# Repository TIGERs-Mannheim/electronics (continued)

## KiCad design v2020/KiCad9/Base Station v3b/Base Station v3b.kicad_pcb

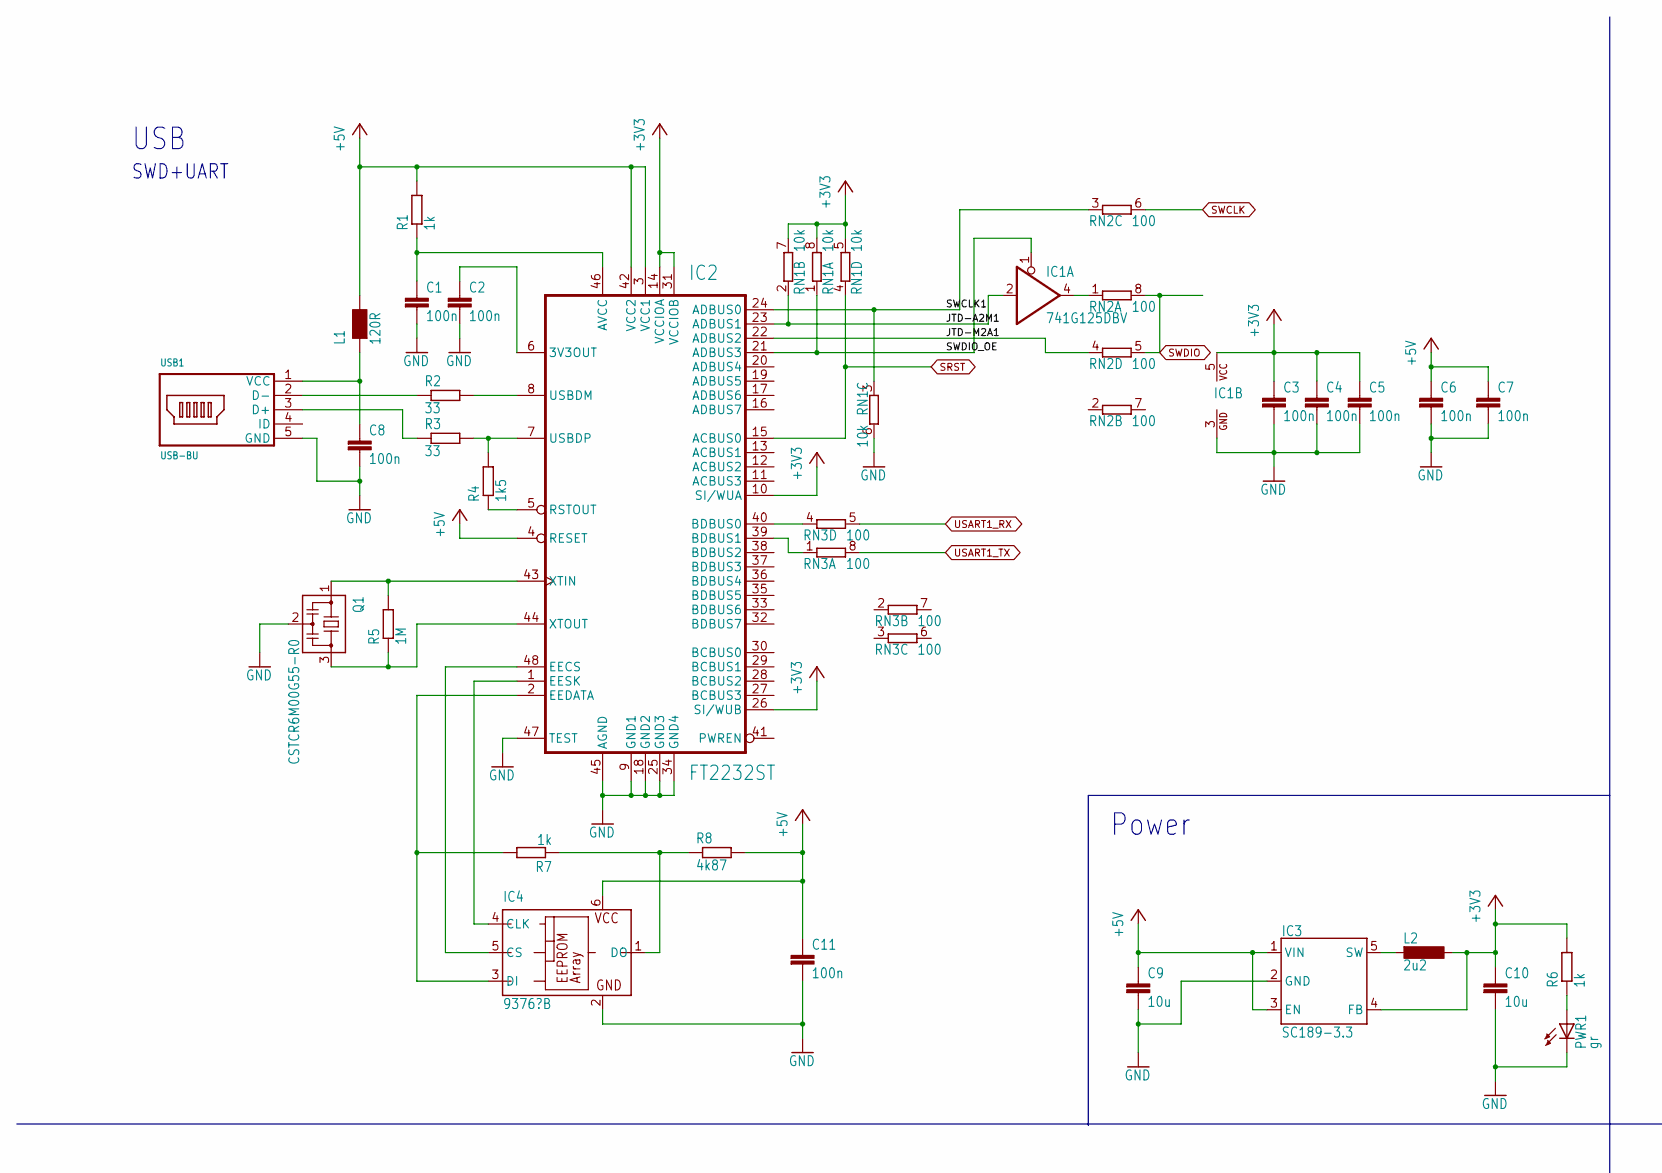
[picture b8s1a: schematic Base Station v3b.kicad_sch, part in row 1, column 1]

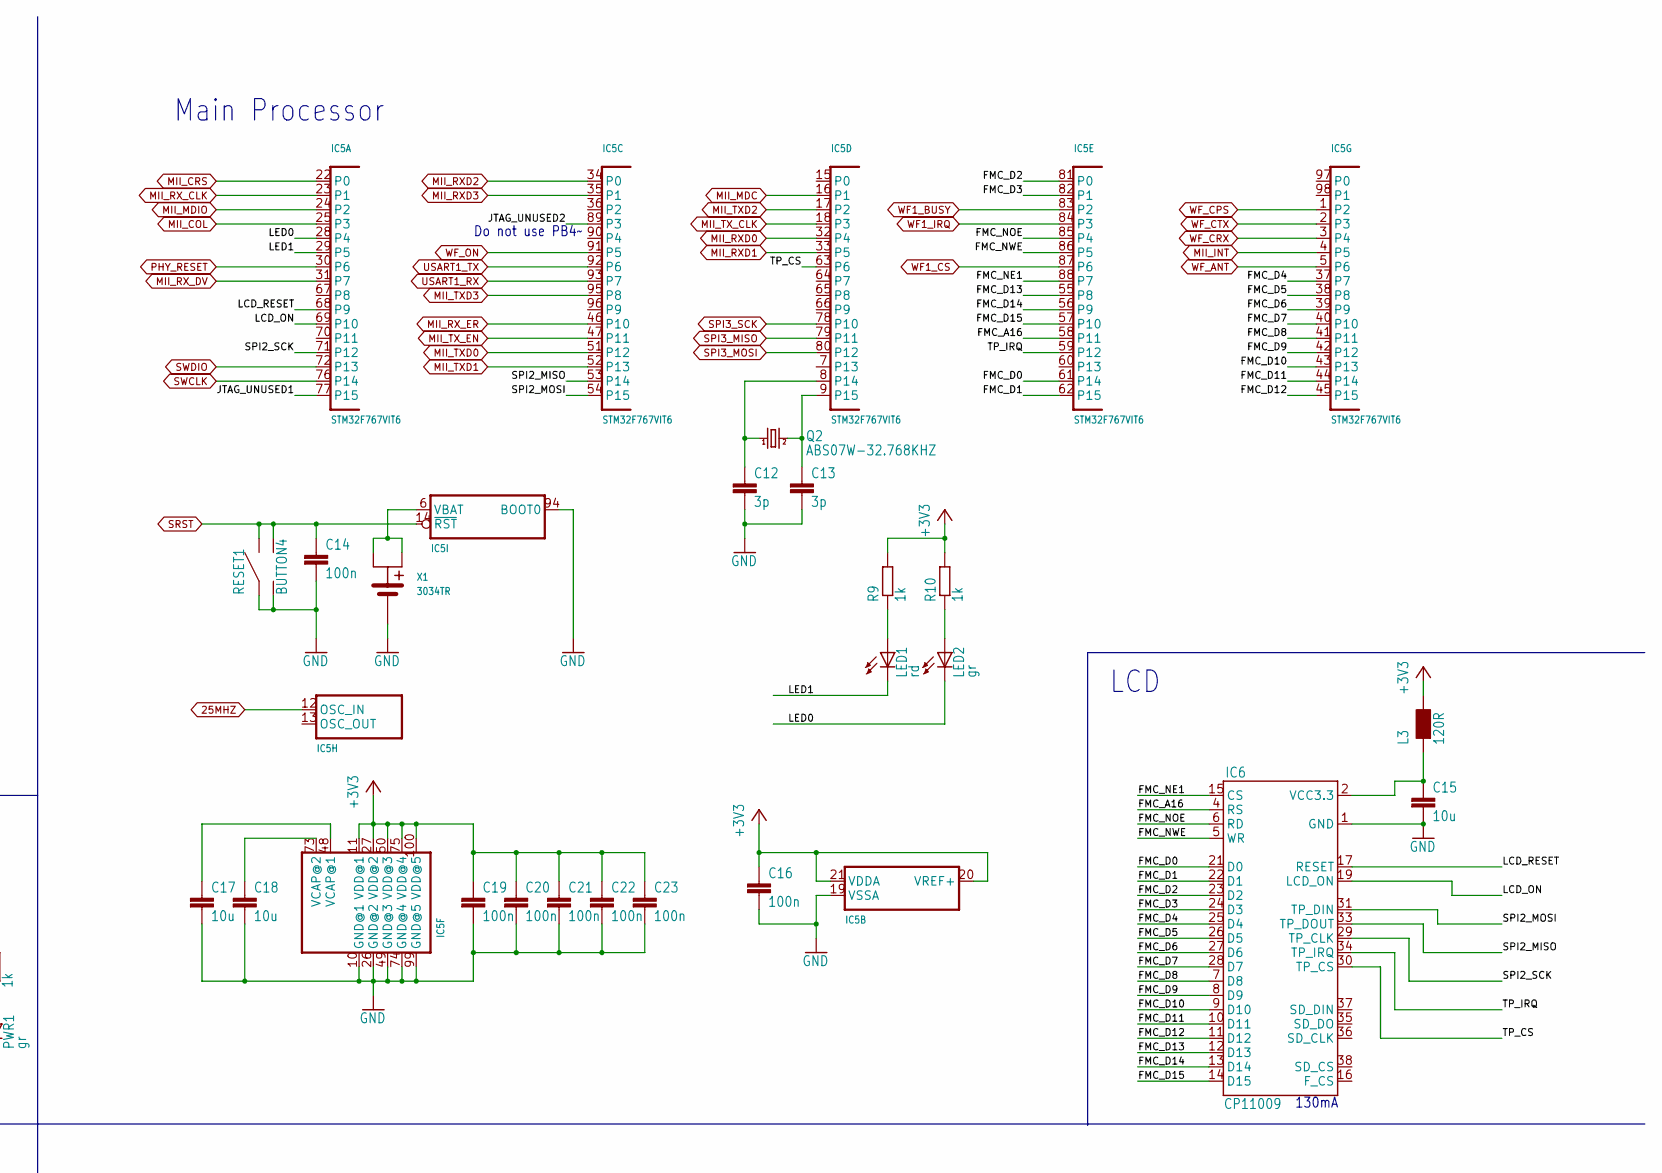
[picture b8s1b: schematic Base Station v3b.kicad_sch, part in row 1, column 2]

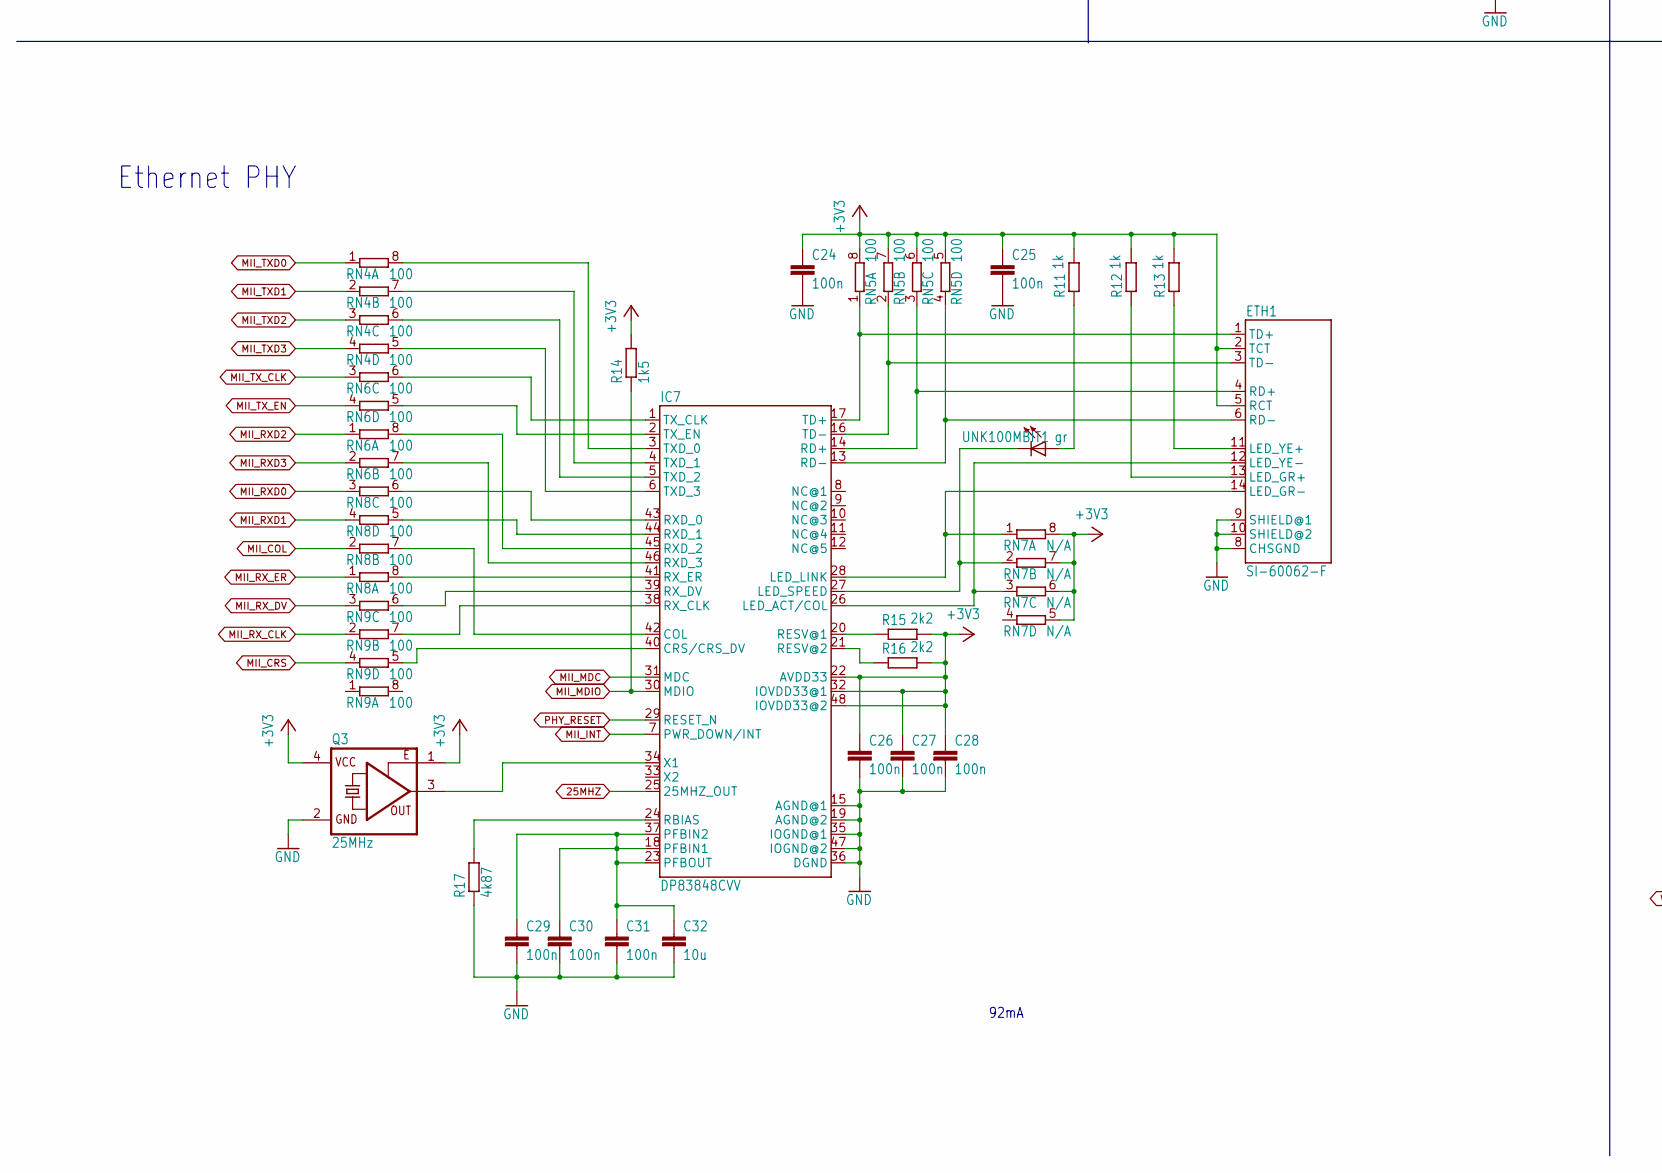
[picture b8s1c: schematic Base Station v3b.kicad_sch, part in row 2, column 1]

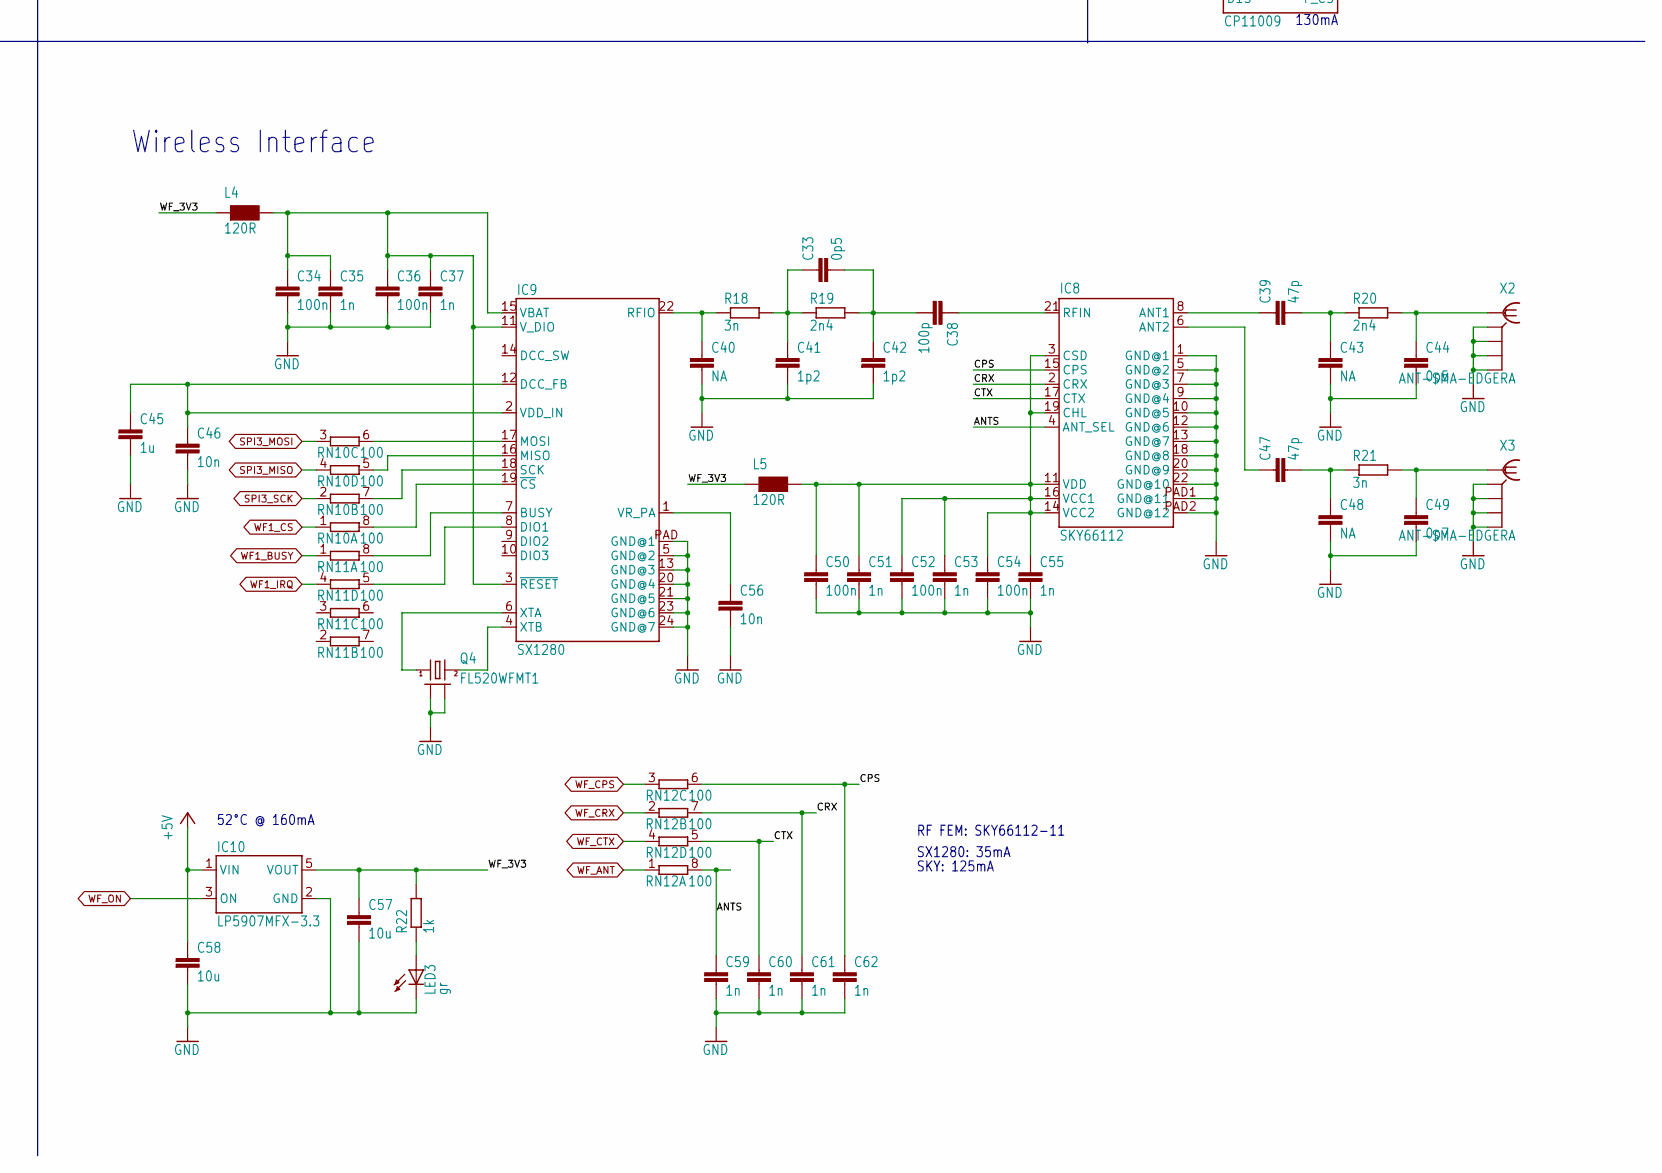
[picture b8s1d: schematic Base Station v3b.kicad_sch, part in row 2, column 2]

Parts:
C1, C2, C3, C4, C5, C6, C7, C8, C11, C14, C16, C19, C20, C21, C22, C23, C24, C25, C26, C27, C28, C29, C30, C31, C34, C36, C50, C52, C54: 100n; C0603
C9, C10, C15, C17, C18, C32, C57, C58: 10u; C0603
C12, C13: 3p; C0603
C33, C44: 0p5; C0402
C35, C37, C51, C53, C55, C59, C60, C61, C62: 1n; C0603
C38: 100p; C0402
C39, C47: 47p; C0402
C40, C43, C48: NA; C0402
C41, C42: 1p2; C0402
C45: 1u; C0603
C46, C56: 10n; C0603
C49: 0p7; C0402
ETH1: SI-60062-F; RJ45-LED
IC1: 741G125DBV; SOT23-5
IC2: FT2232ST; LQFP48-ST
IC3: SC189-3.3; SOT23-5
IC4: 9376?B; SOT23-6
IC5: STM32F767VIT6; LQFP100-ST
IC6: CP11009; CP11009-THX
IC7: DP83848CVV; LQFP48
IC8: SKY66112; SMCM-22
IC9: SX1280; QFN24L
IC10: LP5907MFX-3.3; SOT23-5L
L1, L3, L4, L5: 120R; 0603
L2: 2u2; IHLP1616
LED1: rd; CHIP-LED0603
LED2, LED3: gr; CHIP-LED0603
PWR1: gr; CHIP-LED0603
Q1: CSTCR6M00G55-R0; CSTCR6M
Q2: ABS07W-32.768KHZ; CRYSTAL-07W
Q3: 25MHz; 7X
Q4: FL520WFMT1; CRYSTAL-7M
R1, R6, R7, R9, R10, R11, R12, R13, R22: 1k; R0603
R2, R3: 33; R0603
R4, R14: 1k5; R0603
R5: 1M; R0603
R8, R17: 4k87; R0603
R15, R16: 2k2; R0603
R18, R21: 3n; R0402
R19, R20: 2n4; R0402
RESET1: BUTTON4
RN1: 10k; EXB28V
RN2, RN3, RN4, RN5, RN6, RN8, RN9, RN10, RN11, RN12: 100; EXB28V
RN7: N/A; EXB28V
UNK100MBIT1: gr; CHIP-LED0603
USB1: USB-BU; USB-BMICRO
X1: 3034TR; CR2025
X2, X3: ANT-SMA-EDGERA; ANT-SMA-RA

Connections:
25MHZ: IC5.12 (OSC_IN), IC7.25 (25MHZ_OUT)
+3V3: C3.1, C4.1, C5.1, C10.1, C16.1, C19.1, C20.1, C21.1, C22.1, C23.1, C24.1, C25.1, C26.1, C27.1, C28.1, ETH1.2 (TCT), ETH1.5 (RCT), IC1.5 (VCC), IC2.10 (SI/WUA), IC2.14 (VCCIOA), IC2.26 (SI/WUB), IC2.31 (VCCIOB), IC3.4 (FB), IC5.11 (VDD@1), IC5.20 (VREF+), IC5.21 (VDDA), IC5.27 (VDD@2), IC5.50 (VDD@3), IC5.75 (VDD@4), IC5.100 (VDD@5), IC7.22 (AVDD33), IC7.32 (IOVDD33@1), IC7.48 (IOVDD33@2), L2.P$1 (1), L3.2, Q3.1 (OE), Q3.4 (VCC), R6.2, R9.2, R10.2, R11.2, R12.2, R13.2, R14.2, R15.2, R16.2, RN1.5 (2), RN1.7 (2), RN1.8 (2), RN5.5 (2), RN5.6 (2), RN5.7 (2), RN5.8 (2), RN7.5 (2), RN7.6 (2), RN7.7 (2), RN7.8 (2); also elsewhere on the board
+5V: C6.1, C7.1, C9.1, C11.1, C58.1, IC2.3 (VCC1), IC2.4 (RESET), IC2.42 (VCC2), IC3.1 (VIN), IC3.3 (EN), IC4.6 (VCC), IC10.1 (VIN), L1.2, R1.2, R8.2
ANTS: C59.1, IC8.4 (ANT_SEL), RN12.8 (2)
CPS: C62.1, IC8.15 (CPS), RN12.6 (2)
CRX: C61.1, IC8.2 (CRX), RN12.7 (2)
CTX: C60.1, IC8.17 (CTX), RN12.5 (2)
FMC_A16: IC5.58 (P11), IC6.4 (RS)
FMC_D0: IC5.61 (P14), IC6.21 (D0)
FMC_D1: IC5.62 (P15), IC6.22 (D1)
FMC_D2: IC5.81 (P0), IC6.23 (D2)
FMC_D3: IC5.82 (P1), IC6.24 (D3)
FMC_D4: IC5.37 (P7), IC6.25 (D4)
FMC_D5: IC5.38 (P8), IC6.26 (D5)
FMC_D6: IC5.39 (P9), IC6.27 (D6)
FMC_D7: IC5.40 (P10), IC6.28 (D7)
FMC_D8: IC5.41 (P11), IC6.7 (D8)
FMC_D9: IC5.42 (P12), IC6.8 (D9)
FMC_D10: IC5.43 (P13), IC6.9 (D10)
FMC_D11: IC5.44 (P14), IC6.10 (D11)
FMC_D12: IC5.45 (P15), IC6.11 (D12)
FMC_D13: IC5.55 (P8), IC6.12 (D13)
FMC_D14: IC5.56 (P9), IC6.13 (D14)
FMC_D15: IC5.57 (P10), IC6.14 (D15)
FMC_NE1: IC5.88 (P7), IC6.15 (CS)
FMC_NOE: IC5.85 (P4), IC6.6 (RD)
FMC_NWE: IC5.86 (P5), IC6.5 (WR)
GND: C1.2, C2.2, C3.2, C4.2, C5.2, C6.2, C7.2, C8.2, C9.2, C10.2, C11.2, C12.2, C13.2, C14.2, C15.2, C16.2, C17.2, C18.2, C19.2, C20.2, C21.2, C22.2, C23.2, C24.2, C25.2, C26.2, C27.2, C28.2, C29.2, C30.2, C31.2, C32.2, C34.2, C35.2, C36.2, C37.2, C40.2, C41.2, C42.2, C43.2, C44.2, C45.2, C46.2, C48.2, C49.2, C50.2, C51.2, C52.2, C53.2, C54.2, C55.2, C56.2, C57.2, C58.2, C59.2, C60.2, C61.2, C62.2, ETH1.8 (CHSGND), ETH1.9 (SHIELD@1), ETH1.10 (SHIELD@2), IC1.3 (GND), IC2.9 (GND1), IC2.18 (GND2), IC2.25 (GND3), IC2.34 (GND4), IC2.45 (AGND), IC2.47 (TEST), IC3.2 (GND), IC4.2 (GND), IC5.10 (GND@1), IC5.19 (VSSA), IC5.26 (GND@2), IC5.49 (GND@3), IC5.74 (GND@4), IC5.94 (BOOT0), IC5.99 (GND@5), IC6.1 (GND), IC7.15 (AGND@1), IC7.19 (AGND@2), IC7.35 (IOGND@1), IC7.36 (DGND), IC7.47 (IOGND@2), IC8.1 (GND@1), IC8.5 (GND@2), IC8.7 (GND@3), IC8.9 (GND@4), IC8.10 (GND@5), IC8.12 (GND@6), IC8.13 (GND@7), IC8.18 (GND@8), IC8.20 (GND@9), IC8.22 (GND@10), IC8.PAD1 (GND@11), IC8.PAD2 (GND@12), IC9.5 (GND@2), IC9.13 (GND@3), IC9.20 (GND@4), IC9.21 (GND@5), IC9.23 (GND@6), IC9.24 (GND@7), IC9.PAD (GND@1), IC10.2 (GND), LED3.C, PWR1.C, Q1.2, Q3.2 (GND), Q4.2 (GND1), Q4.4 (GND2), R17.1, RESET1.1, RESET1.2, RN1.6 (2), USB1.5 (GND), X1.GND, X2.GND1 (GND), X2.GND2 (GND1), X2.GND3 (GND2), X2.GND4 (GND3), X3.GND1 (GND), X3.GND2 (GND1), X3.GND3 (GND2), X3.GND4 (GND3); also elsewhere on the board
JTAG_UNUSED1: IC5.77 (P15)
JTAG_UNUSED2: IC5.89 (P3)
JTD-A2M1: IC1.2 (I), IC2.23 (ADBUS1), RN1.2 (1)
JTD-M2A1: IC2.22 (ADBUS2), RN2.4 (1)
LCD_ON: IC5.69 (P10), IC6.19 (LCD_ON)
LCD_RESET: IC5.68 (P9), IC6.17 (RESET)
LED0: IC5.28 (P4), LED2.C
LED1: IC5.29 (P5), LED1.C
MII_COL: IC5.25 (P3), RN8.2 (1)
MII_CRS: IC5.22 (P0), RN9.4 (1)
MII_INT: IC5.4 (P5), IC7.7 (PWR_DOWN/INT)
MII_MDC: IC5.16 (P1), IC7.31 (MDC)
MII_MDIO: IC5.24 (P2), IC7.30 (MDIO), R14.1
MII_RXD0: IC5.32 (P4), RN8.3 (1)
MII_RXD1: IC5.33 (P5), RN8.4 (1)
MII_RXD2: IC5.34 (P0), RN6.1
MII_RXD3: IC5.35 (P1), RN6.2 (1)
MII_RX_CLK: IC5.23 (P1), RN9.2 (1)
MII_RX_DV: IC5.31 (P7), RN9.3 (1)
MII_RX_ER: IC5.46 (P10), RN8.1
MII_TXD0: IC5.51 (P12), RN4.1
MII_TXD1: IC5.52 (P13), RN4.2 (1)
MII_TXD2: IC5.17 (P2), RN4.3 (1)
MII_TXD3: IC5.95 (P8), RN4.4 (1)
MII_TX_CLK: IC5.18 (P3), RN6.3 (1)
MII_TX_EN: IC5.47 (P11), RN6.4 (1)
unnamed: IC9.17 (MOSI), RN10.6 (2)
unnamed: IC9.16 (MISO), RN10.5 (2)
unnamed: IC9.18 (SCK), RN10.7 (2)
unnamed: IC9.19 (~CS), RN10.8 (2)
unnamed: IC9.7 (BUSY), RN11.8 (2)
unnamed: C18.1, IC5.73 (VCAP@2)
unnamed: IC9.8 (DIO1), RN11.5 (2)
unnamed: IC2.48 (EECS), IC4.5 (CS)
unnamed: IC2.1 (EESK), IC4.4 (CLK)
unnamed: IC7.3 (TXD_0), RN4.8 (2)
unnamed: IC7.4 (TXD_1), RN4.7 (2)
unnamed: IC7.5 (TXD_2), RN4.6 (2)
unnamed: IC2.2 (EEDATA), IC4.3 (DI), R7.2
unnamed: IC7.6 (TXD_3), RN4.5 (2)
unnamed: IC7.1 (TX_CLK), RN6.6 (2)
unnamed: IC7.2 (TX_EN), RN6.5 (2)
unnamed: IC7.45 (RXD_2), RN6.8 (2)
unnamed: LED3.A, R22.1
unnamed: IC2.44 (XTOUT), Q1.3, R5.1
unnamed: IC4.1 (DO), R7.1, R8.1
unnamed: IC7.46 (RXD_3), RN6.7 (2)
unnamed: C17.1, IC5.48 (VCAP@1)
unnamed: IC7.43 (RXD_0), RN8.6 (2)
unnamed: IC7.44 (RXD_1), RN8.5 (2)
unnamed: IC7.42 (COL), RN8.7 (2)
unnamed: IC7.41 (RX_ER), RN8.8 (2)
unnamed: IC7.39 (RX_DV), RN9.6 (2)
unnamed: IC7.38 (RX_CLK), RN9.7 (2)
unnamed: IC7.40 (CRS/CRS_DV), RN9.5 (2)
unnamed: IC7.24 (RBIAS), R17.2
unnamed: C29.1, C30.1, C31.1, C32.1, IC7.18 (PFBIN1), IC7.23 (PFBOUT), IC7.37 (PFBIN2)
unnamed: IC7.20 (RESV@1), R15.1
unnamed: IC7.21 (RESV@2), R16.1
unnamed 87: ETH1.12 (LED_YE-), IC7.26 (LED_ACT/COL), RN7.3 (1); also elsewhere on the board
unnamed 88: IC7.27 (LED_SPEED), RN7.2 (1), UNK100MBIT1.C; also elsewhere on the board
unnamed 89: ETH1.14 (LED_GR-), IC7.28 (LED_LINK), RN7.1; also elsewhere on the board
unnamed 90: ETH1.6 (RD-), IC7.13 (RD-), RN5.4 (1); also elsewhere on the board
unnamed 91: PWR1.A, R6.1; also elsewhere on the board
unnamed 92: ETH1.4 (RD+), IC7.14 (RD+), RN5.3 (1); also elsewhere on the board
unnamed 93: ETH1.3 (TD-), IC7.16 (TD-), RN5.2 (1); also elsewhere on the board
unnamed 94: ETH1.1 (TD+), IC7.17 (TD+), RN5.1; also elsewhere on the board
unnamed 95: R11.1, UNK100MBIT1.A; also elsewhere on the board
unnamed 96: ETH1.13 (LED_GR+), R12.1; also elsewhere on the board
unnamed 97: ETH1.11 (LED_YE+), R13.1; also elsewhere on the board
unnamed: IC7.34 (X1), Q3.3 (FO)
unnamed: IC1.4 (O), RN2.1
unnamed: LED2.A, R10.1
unnamed: LED1.A, R9.1
unnamed: IC2.40 (BDBUS0), RN3.4 (1)
unnamed: IC2.39 (BDBUS1), RN3.1
unnamed: C15.1, IC6.2 (VCC3.3), L3.1
unnamed: IC9.6 (XTA), Q4.1
unnamed: IC9.4 (XTB), Q4.3 (2)
unnamed: C33.1, C41.1, R18.2, R19.1
unnamed: C33.2, C38.2, C42.1, R19.2
unnamed: C56.1, IC9.1 (VR_PA)
unnamed: C45.1, C46.1, IC9.2 (VDD_IN), IC9.12 (DCC_FB)
unnamed: C38.1, IC8.21 (RFIN)
unnamed: C39.2, C43.1, R20.1
unnamed: C44.1, R20.2, X2.C (1)
unnamed: C47.2, C48.1, R21.1
unnamed: C49.1, R21.2, X3.C (1)
unnamed: C39.1, IC8.8 (ANT1)
unnamed: C47.1, IC8.6 (ANT2)
unnamed: IC2.7 (USBDP), R3.2, R4.2
unnamed: IC2.8 (USBDM), R2.2
unnamed: IC2.5 (RSTOUT), R4.1
unnamed: C2.1, IC2.6 (3V3OUT)
unnamed: C8.1, L1.1, USB1.1 (VCC)
unnamed: R2.1, USB1.2 (D-)
unnamed: R3.1, USB1.3 (D+)
unnamed: C1.1, IC2.46 (AVCC), R1.1
unnamed: IC2.43 (XTIN), Q1.1, R5.2
OSC32_IN: C12.1, IC5.8 (P14), Q2.1
OSC32_OUT: C13.1, IC5.9 (P15), Q2.2
PHY_RESET: IC5.30 (P6), IC7.29 (RESET_N)
RFIO1: C40.1, IC9.22 (RFIO), R18.1
SPI2_MISO: IC5.53 (P14), IC6.33 (TP_DOUT)
SPI2_MOSI: IC5.54 (P15), IC6.31 (TP_DIN)
SPI2_SCK: IC5.71 (P12), IC6.29 (TP_CLK)
SPI3_MISO: IC5.79 (P11), RN10.4 (1)
SPI3_MOSI: IC5.80 (P12), RN10.3 (1)
SPI3_SCK: IC5.78 (P10), RN10.2 (1)
SRST: C14.1, IC2.15 (ACBUS0), IC5.14 (~RST), RESET1.3, RESET1.4, RN1.4 (1)
SW-OUT: IC3.5 (SW), L2.P$2 (2)
SWCLK: IC5.76 (P14), RN2.6 (2)
SWCLK1: IC2.24 (ADBUS0), RN1.3 (1), RN2.3 (1)
SWDIO: IC5.72 (P13), RN2.5 (2), RN2.8 (2)
SWDIO_OE: IC1.1 (OE), IC2.21 (ADBUS3), RN1.1
TP_CS: IC5.63 (P6), IC6.30 (TP_CS)
TP_IRQ: IC5.59 (P12), IC6.34 (TP_IRQ)
USART1_RX: IC5.93 (P7), RN3.5 (2)
USART1_TX: IC5.92 (P6), RN3.8 (2)
VBAT: IC5.6 (VBAT), X1.POS1, X1.POS2
WF1_BUSY: IC5.83 (P2), RN11.1
WF1_CS: IC5.87 (P6), RN10.1
WF1_IRQ: IC5.84 (P3), RN11.4 (1)
WF_3V3: C57.1, IC10.5 (VOUT), L4.1, L5.1, R22.2
WF_3V3FEM: C50.1, C51.1, C52.1, C53.1, C54.1, C55.1, IC8.3 (CSD), IC8.11 (VDD), IC8.14 (VCC2), IC8.16 (VCC1), IC8.19 (CHL), L5.2
WF_3V3SX: C34.1, C35.1, C36.1, C37.1, IC9.3 (~RESET), IC9.11 (V_DIO), IC9.15 (VBAT), L4.2
WF_ANT: IC5.5 (P6), RN12.1
WF_CPS: IC5.1 (P2), RN12.3 (1)
WF_CRX: IC5.3 (P4), RN12.2 (1)
WF_CTX: IC5.2 (P3), RN12.4 (1)
WF_ON: IC5.91 (P5), IC10.3 (ON)

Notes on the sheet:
LCD
SX1280: 35mA
Do not use PB4~~{}
USB
52°C @ 160mA
Ethernet PHY
Wireless Interface
Main Processor
SWD+UART
92mA
130mA
SKY: 125mA
Power
RF FEM: SKY66112-11

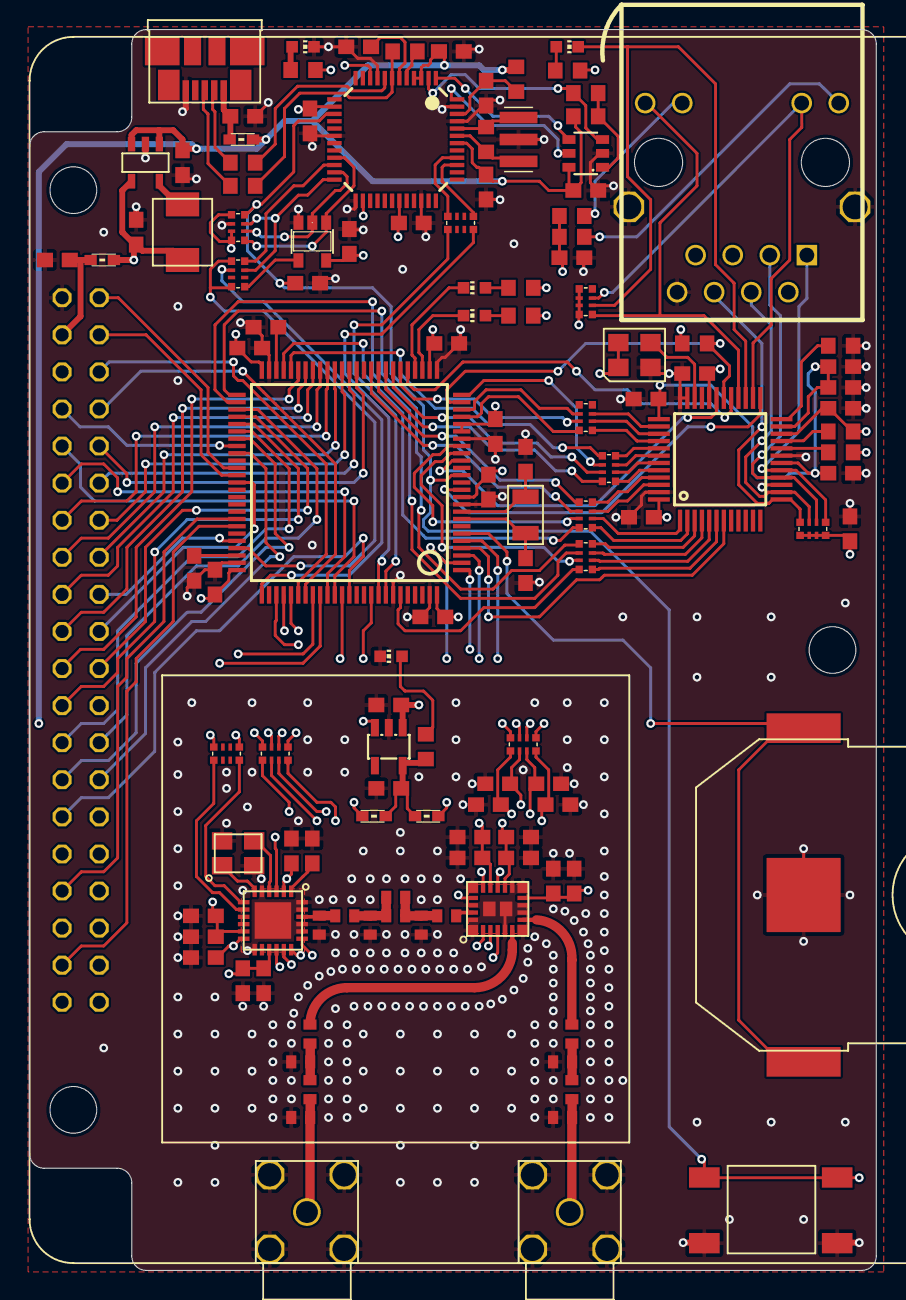
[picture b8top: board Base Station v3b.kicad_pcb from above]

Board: 4 copper layers, 58.0 x 85.0 mm, 130 parts (0 on the bottom side), 157 nets.

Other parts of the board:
ETH0: SI-60062-F; RJ45-LED
PWR0: gr; CHIP-LED0603
U$1: BMI-S-204-F; SHIELD-32MM
UNK100MBIT0: gr; CHIP-LED0603
UNK_HOLE_0: dummyfp0
UNK_HOLE_1: dummyfp1
UNK_HOLE_2: dummyfp2

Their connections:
+3V3: ETH0.2, ETH0.5; also elsewhere on the board
GND: ETH0.8, ETH0.9, ETH0.10, PWR0.C; also elsewhere on the board
unnamed 87: ETH0.12; also elsewhere on the board
unnamed 88: UNK100MBIT0.C; also elsewhere on the board
unnamed 89: ETH0.14; also elsewhere on the board
unnamed 90: ETH0.6; also elsewhere on the board
unnamed 91: PWR0.A; also elsewhere on the board
unnamed 92: ETH0.4; also elsewhere on the board
unnamed 93: ETH0.3; also elsewhere on the board
unnamed 94: ETH0.1; also elsewhere on the board
unnamed 95: UNK100MBIT0.A; also elsewhere on the board
unnamed 96: ETH0.13; also elsewhere on the board
unnamed 97: ETH0.11; also elsewhere on the board

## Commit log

2020-04-14 Release files for v2020 electronics
2020-04-17 Update LICENSE
2025-07-08 Added project files for KiCad9 converted from EAGLE
